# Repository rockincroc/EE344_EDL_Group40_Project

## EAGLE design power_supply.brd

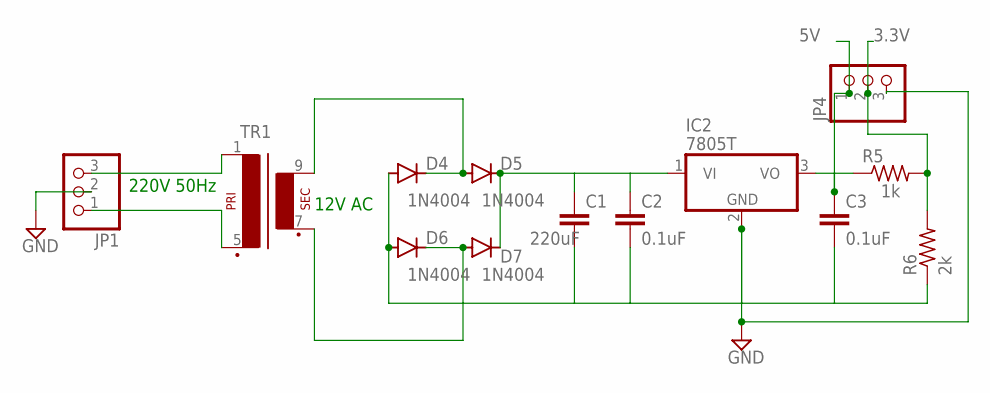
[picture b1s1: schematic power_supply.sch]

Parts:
C1: 220uF; C050-025X075
C2, C3: 0.1uF; C050-025X075
D4, D5, D6, D7: 1N4004; DO41-10
IC2: 7805T; TO220H
JP1, JP4: PINHD-1X3; 1X03
R5: 1k; 0207/10
R6: 2k; 0207/10
TR1: EI30-1

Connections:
3.3V: JP4.2, R5.2, R6.2
5V: C3.1, IC2.3 (VO), JP4.1, R5.1
GND: C1.2, C2.2, C3.2, D4.A, D6.A, IC2.2 (GND), JP1.2, JP4.3, R6.1
unnamed: C1.1, C2.1, D5.C, D7.C, IC2.1 (VI)
unnamed: JP1.3, TR1.1
unnamed: D4.C, D5.A, TR1.9 (S4)
unnamed: D6.C, D7.A, TR1.7 (S3)
unnamed: JP1.1, TR1.5 (P2)

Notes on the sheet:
220V 50Hz
12V AC

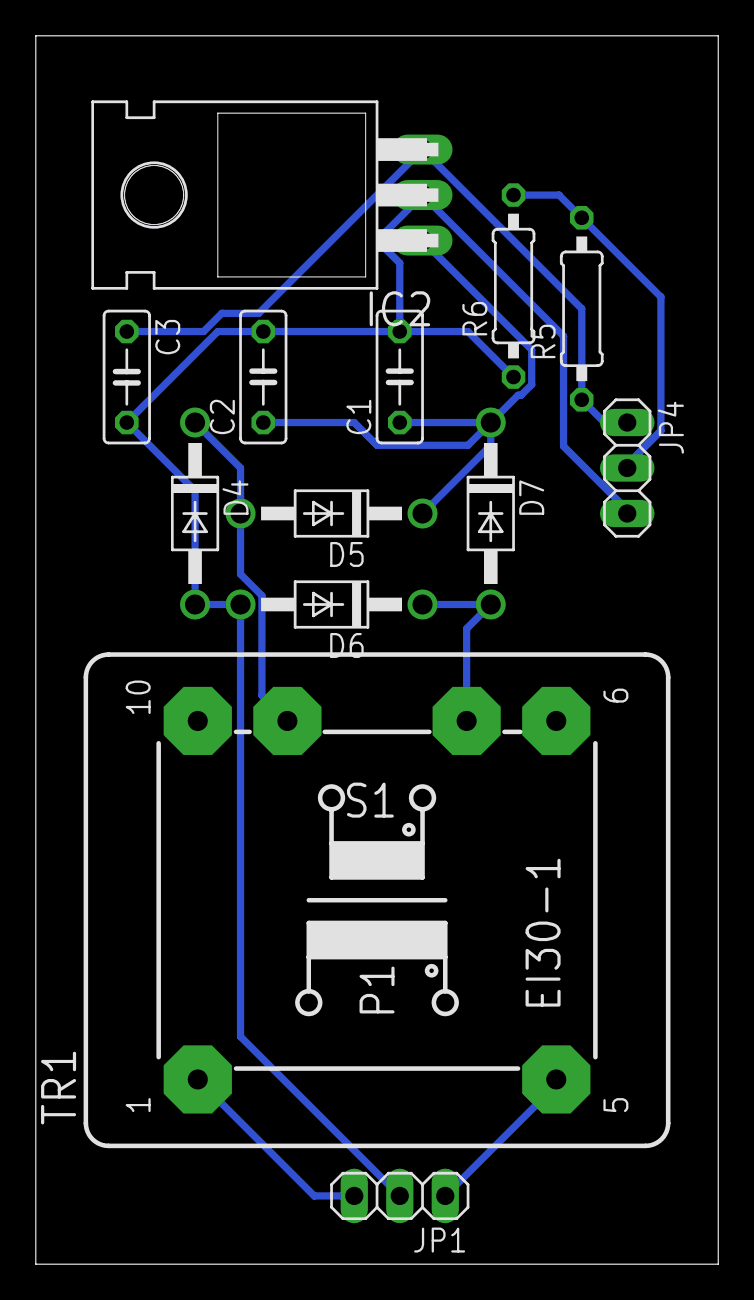
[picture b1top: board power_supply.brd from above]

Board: 2 copper layers, 38.1 x 68.6 mm, 13 parts (0 on the bottom side), 8 nets.

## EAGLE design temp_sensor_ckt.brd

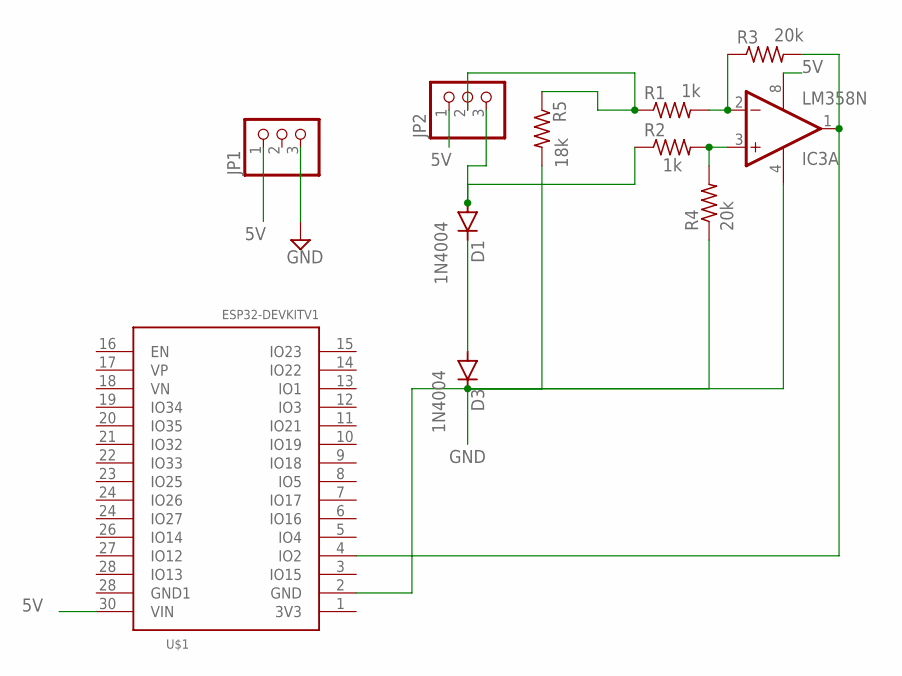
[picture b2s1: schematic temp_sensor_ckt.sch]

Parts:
D1, D3: 1N4004; DO41-10
IC3: LM358N; DIL08
JP1, JP2: PINHD-1X3; 1X03
R1, R2: 1k; 0207/10
R3, R4: 20k; 0207/10
R5: 18k; 0207/10
U$1: ESP32DEVKITV1; ESP32-DEVKITV1

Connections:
5V: IC3.8 (V+), JP1.1, JP2.1, U$1.30 (VIN)
GND: D3.C, IC3.4 (V-), JP1.3, R4.1, R5.2, U$1.2 (GND)
unnamed: D1.A, JP2.3, R2.1
unnamed: D1.C, D3.A
unnamed: IC3.2 (-IN), R1.2, R3.1
unnamed: IC3.3 (+IN), R2.2, R4.2
unnamed: IC3.1 (OUT), R3.2, U$1.4 (IO2)
unnamed: JP2.2, R1.1, R5.1

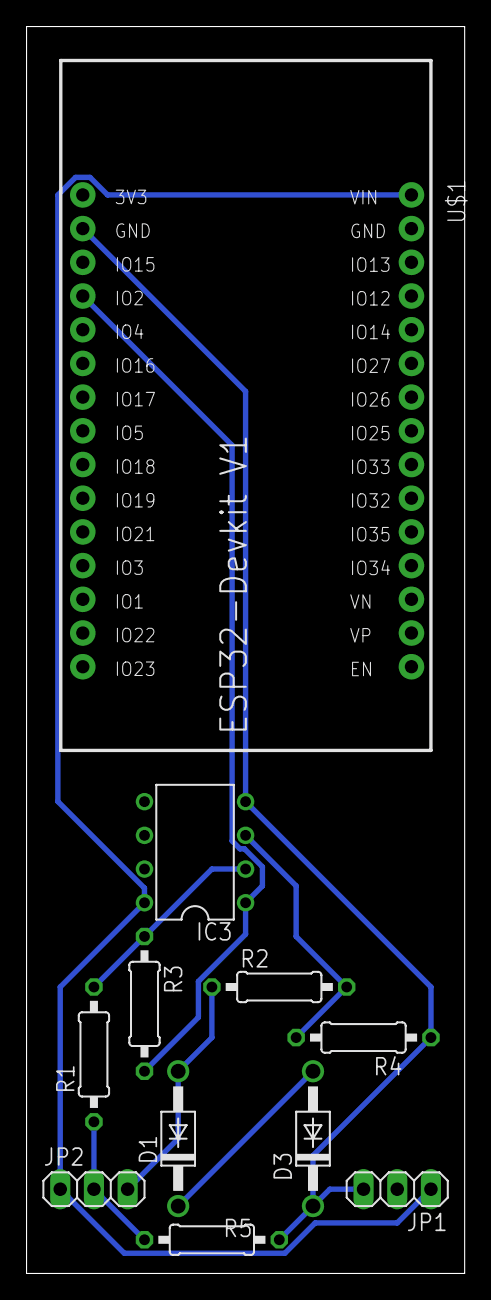
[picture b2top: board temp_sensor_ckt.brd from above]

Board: 2 copper layers, 33.0 x 94.0 mm, 11 parts (0 on the bottom side), 8 nets.

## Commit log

2021-04-03 Create hello
2021-04-04 Rename sketch_apr03b.ino to code_v1_0.ino
2021-04-15 Basic Web Server INO file
2021-04-15 New file - works with ESP32
2021-04-15 Data Backup solution using EEPROM
